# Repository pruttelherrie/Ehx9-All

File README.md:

## WARNING! 
Do not use the EEPROM store code from before 2021-10-01! It will eat up your flash writes like candy because of the braindead EEPROM.write lib in the stm32duino core. Fixed in callbacks.h and main.cpp, dd 2021-10-01

## Ehx9-All: combining and programming EHX '9' pedals

Electro Harmonix' 9 series of pedals is a range of polyphonic synthesis pedals for guitar. The
effects and sounds that can be obtained are superb, however they have a few shortcomings: 
first of all they are not programmable (i.e. there's only one setting, no way to store 
favourites and recall them quickly) and if you have more than one, they tend to take
up quite a lot of space on a pedalboard, especially if one uses them only sparingly
during a set.

The modifications documented in this repository try to eliminate these shortcomings.

## Programmability

To store and recall settings, the pots and switch are removed. GPIOs from the
microcontroller are connected to the main board to replace the functionality of
the pots and the switch. Since we use a PWM signal for the pots, it is low-pass
filtered by a simple first-order RC network.

Encoders take the place of the pots and the switch, a TFT is added for visual 
feedback of the settings.

## Space saving

All pedals of this serie share the same PCB. The difference is in the firmware of the
DSP. This firmware is stored in an EEPROM. By multiplexing multiple EEPROMS on one
board and resetting the DSP after switching the multiplexer, one can switch between
pedals of the series within one enclosure.

## Implementing the mods

Modding a pedal is not for the faint of heart. It is pretty easy to destroy the pedal
in the process. Also, a number of tools are needed:

* A way to program an Attiny2313. I use a Tuxgraphics AVR programmer, but there's a large number of other options.
* A way to program the STM32 blackpill. I use an ST-Link clone.
* There's SMD (de) soldering involved
* The enclosure is modified

## BOM

The BOMs for the PCBs can be found in their folders:
[controller](./controller-pcb/ibom.html)
[multiplexer](./multiplexer-pcb/ibom.html)

## Firmware

The multiplexer firmware was made with the Arduino IDE.

The controller firmware was made with VSCode + PlatformIO.

## Walkthrough of a mod

TBD: text and images.

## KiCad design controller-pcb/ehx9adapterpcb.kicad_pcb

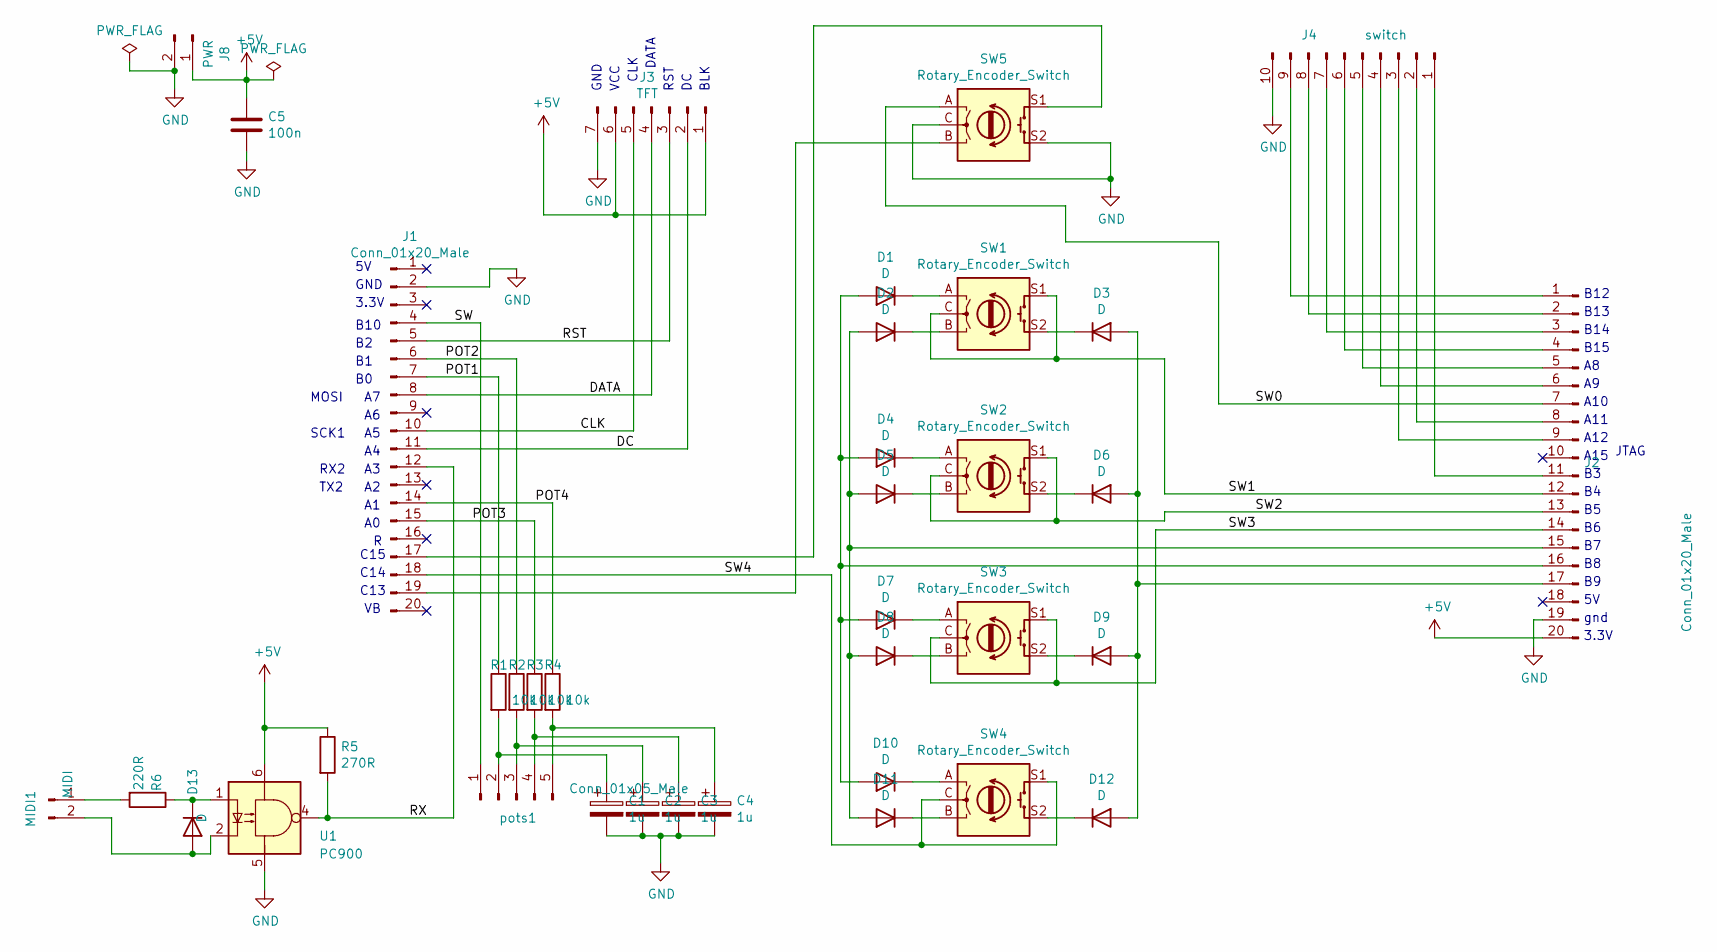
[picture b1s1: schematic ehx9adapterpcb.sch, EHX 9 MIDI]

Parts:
C1, C2, C3, C4: 1u; CP_Radial_D5.0mm_P2.50mm
C5: 100n; C_Rect_L7.0mm_W2.0mm_P5.00mm
D1, D2, D3, D4, D5, D6, D7, D8, D9, D10, D11, D12: D; D_DO-34_SOD68_P7.62mm_Horizontal
D13: D; D_DO-34_SOD68_P2.54mm_Vertical_KathodeUp
J1, J2: Conn_01x20_Male; PinHeader_1x20_P2.54mm_Vertical
J3: TFT; PinHeader_1x07_P2.54mm_Vertical
J4: switch; PinHeader_1x10_P2.54mm_Vertical
J8: PWR; PinHeader_1x02_P2.54mm_Vertical
MIDI1: MIDI; PinHeader_1x02_P2.54mm_Vertical
R1, R2, R3, R4: 10k; R_Axial_DIN0204_L3.6mm_D1.6mm_P2.54mm_Vertical
R5: 270R; R_Axial_DIN0204_L3.6mm_D1.6mm_P2.54mm_Vertical
R6: 220R; R_Axial_DIN0204_L3.6mm_D1.6mm_P2.54mm_Vertical
SW1, SW2, SW3, SW4, SW5: Rotary_Encoder_Switch; RotaryEncoder_Alps_EC11E-Switch_Vertical_H20mm
U1: PC900; DIP-6_W7.62mm_LongPads
pots1: Conn_01x05_Male; PinHeader_1x05_P2.54mm_Vertical

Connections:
+5V: C5.1, J2.20, J3.1, J3.6, J8.1, R5.1, U1.6
/CLK: J1.10, J3.5
/DATA: J1.8, J3.4
/DC: J1.11, J3.2
/POT1: J1.7, R1.1
/POT2: J1.6, R2.1
/POT3: J1.15, R3.1
/POT4: J1.14, R4.1
/RST: J1.5, J3.3
/RX: J1.12, R5.2, U1.4
/SW: J1.4, pots1.1
/SW0: J2.7, SW5.A
/SW1: J2.12, SW1.C, SW1.S1
/SW2: J2.13, SW2.C, SW2.S1
/SW3: J2.14, SW3.C, SW3.S1
/SW4: J1.18, SW4.C, SW4.S1
GND: C1.2, C2.2, C3.2, C4.2, C5.2, J1.2, J2.19, J3.7, J4.10, J8.2, SW5.C, SW5.S2, U1.5
unnamed: C1.1, R1.2, pots1.2
unnamed: C2.1, R2.2, pots1.3
unnamed: C3.1, R3.2, pots1.4
unnamed: C4.1, R4.2, pots1.5
unnamed: D1.1 (K), SW1.A
unnamed: D1.2 (A), D4.2 (A), D7.2 (A), D10.2 (A), J2.16
unnamed: D2.1 (K), SW1.B
unnamed: D3.1 (K), SW1.S2
unnamed: D4.1 (K), SW2.A
unnamed: D5.1 (K), SW2.B
unnamed: D6.1 (K), SW2.S2
unnamed: D7.1 (K), SW3.A
unnamed: D8.1 (K), SW3.B
unnamed: D9.1 (K), SW3.S2
unnamed: D10.1 (K), SW4.A
unnamed: D11.1 (K), SW4.B
unnamed: D2.2 (A), D5.2 (A), D8.2 (A), D11.2 (A), J2.15
unnamed: D12.1 (K), SW4.S2
unnamed: D3.2 (A), D6.2 (A), D9.2 (A), D12.2 (A), J2.17
unnamed: D13.1 (K), R6.1, U1.1
unnamed: D13.2 (A), MIDI1.2, U1.2
unnamed: J1.17, SW5.S1
unnamed: J1.19, SW5.B
unnamed: J2.1, J4.9
unnamed: J2.2, J4.8
unnamed: J2.3, J4.7
unnamed: J2.4, J4.6
unnamed: J2.5, J4.5
unnamed: J2.6, J4.4
unnamed: J2.8, J4.2
unnamed: J2.9, J4.3
unnamed: J2.11, J4.1
unnamed: MIDI1.1, R6.2

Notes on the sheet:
GND
3.3V
B10
C15
C14
C13
gnd
A15
A12
A11
A10
B15
B14
B13
B12
CLK
SCK1
BLK
RST
DATA
MOSI
VCC
TX2
RX2
JTAG

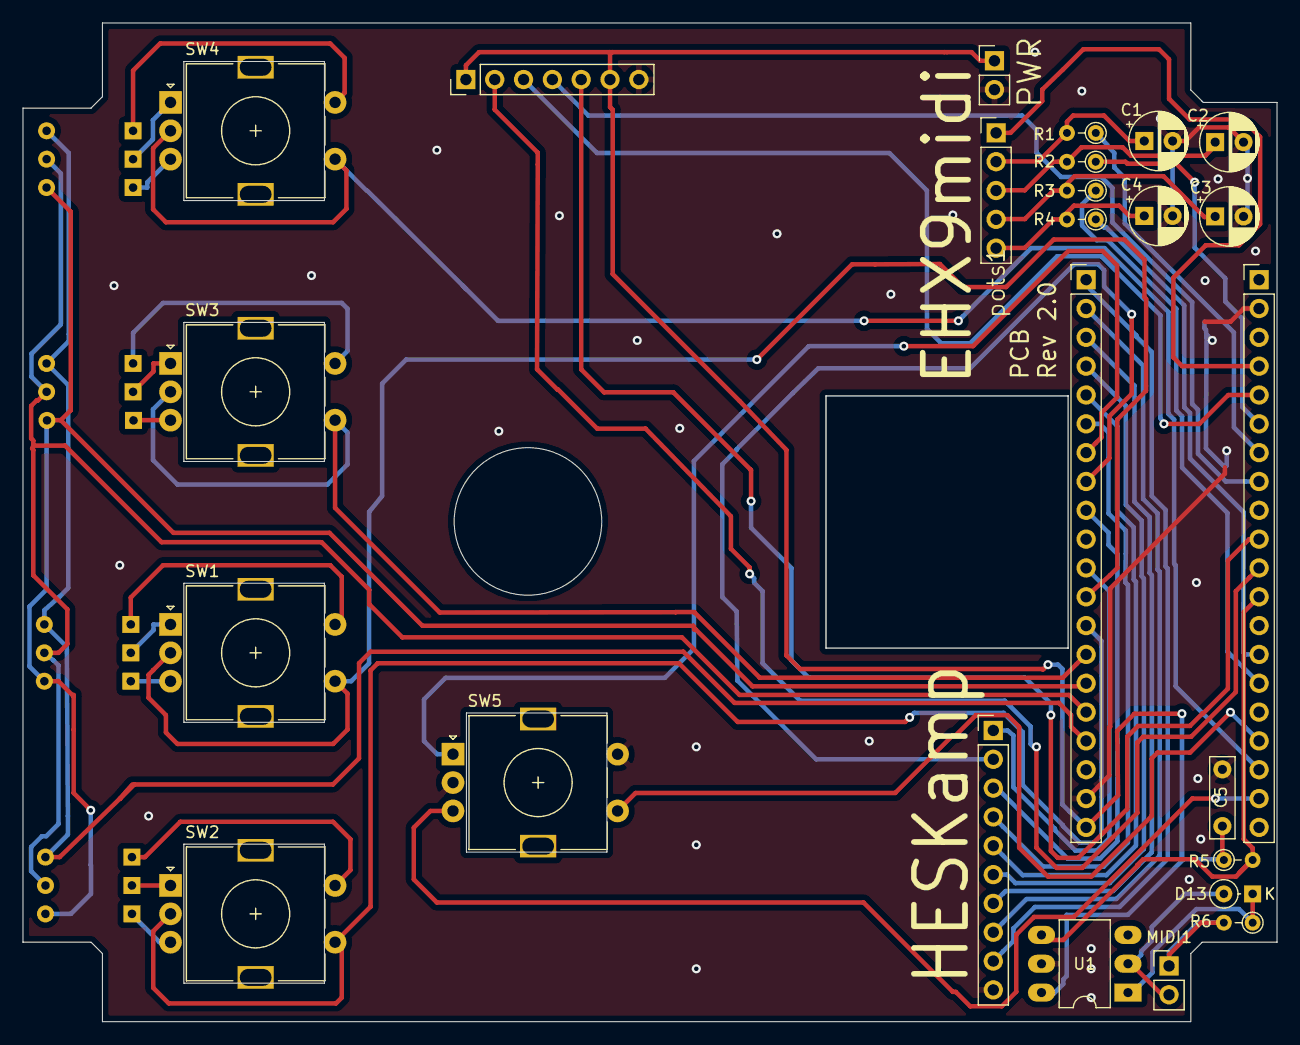
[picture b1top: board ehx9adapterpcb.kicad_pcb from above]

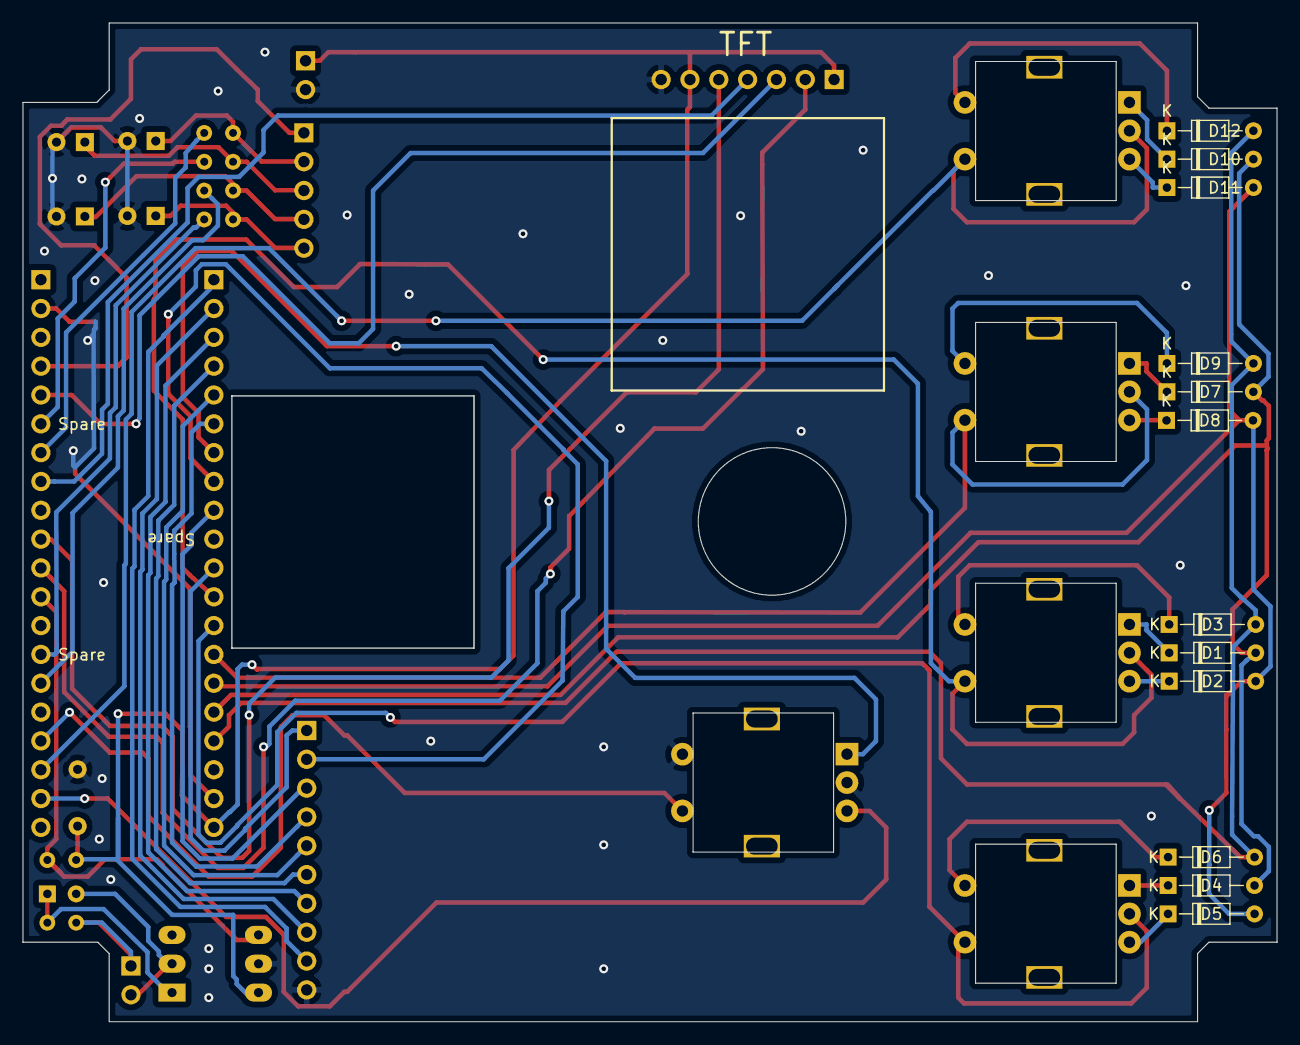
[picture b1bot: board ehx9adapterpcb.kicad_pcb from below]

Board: 2 copper layers, 110.5 x 88.0 mm, 37 parts (12 on the bottom side), 50 nets.

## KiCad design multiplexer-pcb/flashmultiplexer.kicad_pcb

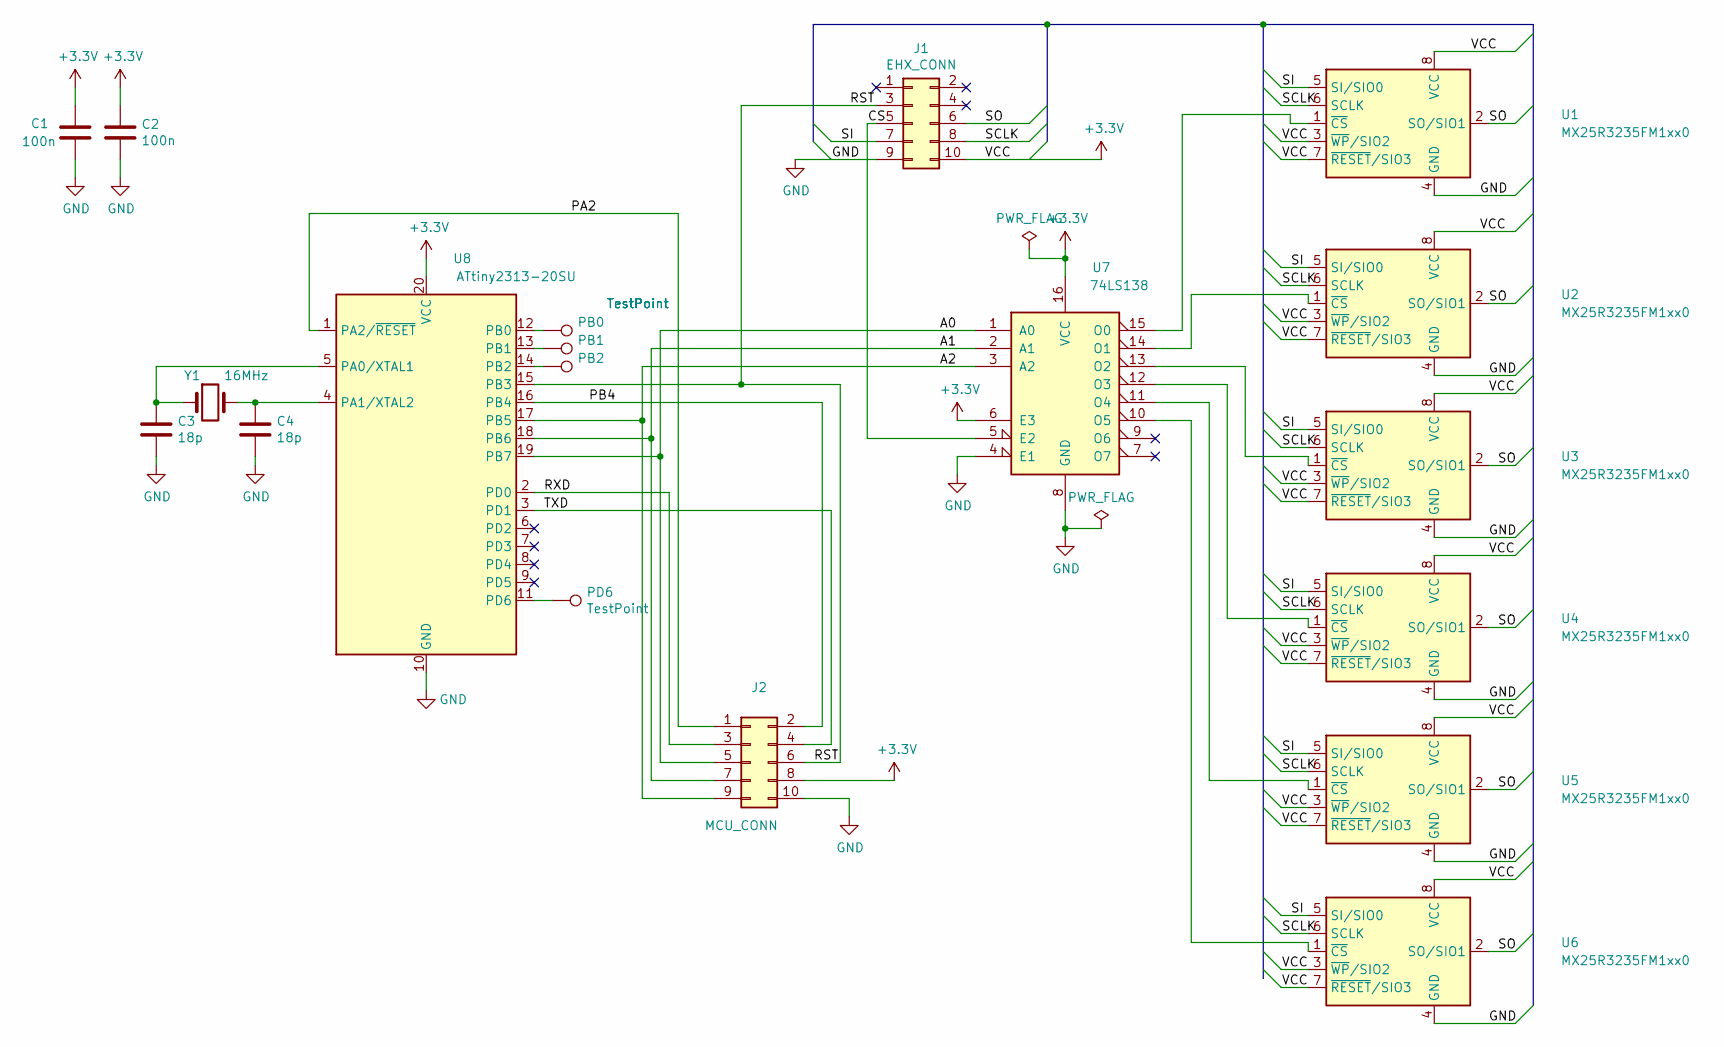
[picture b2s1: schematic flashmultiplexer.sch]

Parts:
C1, C2: 100n; C_1206_3216Metric
C3, C4: 18p; C_0805_2012Metric
J1: EHX_CONN; PinHeader_2x05_P2.54mm_Vertical
J2: MCU_CONN; PinHeader_2x05_P2.54mm_Horizontal
PB0, PB1, PB2: TestPoint; TestPoint_Pad_D1.5mm
PD6: TestPoint; TestPoint_Pad_D1.5mm
U1: MX25R3235FM1xx0; SOP-8_5.28x5.23mm_P1.27mm
U2, U3, U4, U5, U6: MX25R3235FM1xx0; SOP-8_3.9x4.9mm_P1.27mm
U7: 74LS138; SO-16_5.3x10.2mm_P1.27mm
U8: ATtiny2313-20SU; SOIC-20W_7.5x12.8mm_P1.27mm
Y1: 16MHz; Crystal_SMD_7050-2Pin_7.0x5.0mm_HandSoldering

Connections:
+3V3: C1.1, C2.1, J1.10, J2.8, U1.3 (~WP~/SIO2), U1.7 (~RESET~/SIO3), U1.8 (VCC), U2.3 (~WP~/SIO2), U2.7 (~RESET~/SIO3), U2.8 (VCC), U3.3 (~WP~/SIO2), U3.7 (~RESET~/SIO3), U3.8 (VCC), U4.3 (~WP~/SIO2), U4.7 (~RESET~/SIO3), U4.8 (VCC), U5.3 (~WP~/SIO2), U5.7 (~RESET~/SIO3), U5.8 (VCC), U6.3 (~WP~/SIO2), U6.7 (~RESET~/SIO3), U6.8 (VCC), U7.6 (E3), U7.16 (VCC), U8.20 (VCC)
/A0: J2.5, U7.1 (A0), U8.19 (PB7)
/A1: J2.7, U7.2 (A1), U8.18 (PB6)
/A2: J2.9, U7.3 (A2), U8.17 (PB5)
/CS: J1.5, U7.5 (E2)
/PA2: J2.1, U8.1 (PA2/~RESET)
/PB4: J2.2, U8.16 (PB4)
/RST: J1.3, J2.6, U8.15 (PB3)
/RXD: J2.3, U8.2 (PD0)
/SCLK: J1.8, U1.6 (SCLK), U2.6 (SCLK), U3.6 (SCLK), U4.6 (SCLK), U5.6 (SCLK), U6.6 (SCLK)
/SI: J1.7, U1.5 (SI/SIO0), U2.5 (SI/SIO0), U3.5 (SI/SIO0), U4.5 (SI/SIO0), U5.5 (SI/SIO0), U6.5 (SI/SIO0)
/SO: J1.6, U1.2 (SO/SIO1), U2.2 (SO/SIO1), U3.2 (SO/SIO1), U4.2 (SO/SIO1), U5.2 (SO/SIO1), U6.2 (SO/SIO1)
/TXD: J2.4, U8.3 (PD1)
GND: C1.2, C2.2, C3.2, C4.2, J1.9, J2.10, U1.4 (GND), U2.4 (GND), U3.4 (GND), U4.4 (GND), U5.4 (GND), U6.4 (GND), U7.4 (E1), U7.8 (GND), U8.10 (GND)
unnamed: C3.1, U8.5 (PA0/XTAL1), Y1.1
unnamed: C4.1, U8.4 (PA1/XTAL2), Y1.2
unnamed: PB0.1, U8.12 (PB0)
unnamed: PB1.1, U8.13 (PB1)
unnamed: PB2.1, U8.14 (PB2)
unnamed: PD6.1, U8.11 (PD6)
unnamed: U1.1 (~CS), U7.15 (O0)
unnamed: U2.1 (~CS), U7.14 (O1)
unnamed: U3.1 (~CS), U7.13 (O2)
unnamed: U4.1 (~CS), U7.12 (O3)
unnamed: U5.1 (~CS), U7.11 (O4)
unnamed: U6.1 (~CS), U7.10 (O5)

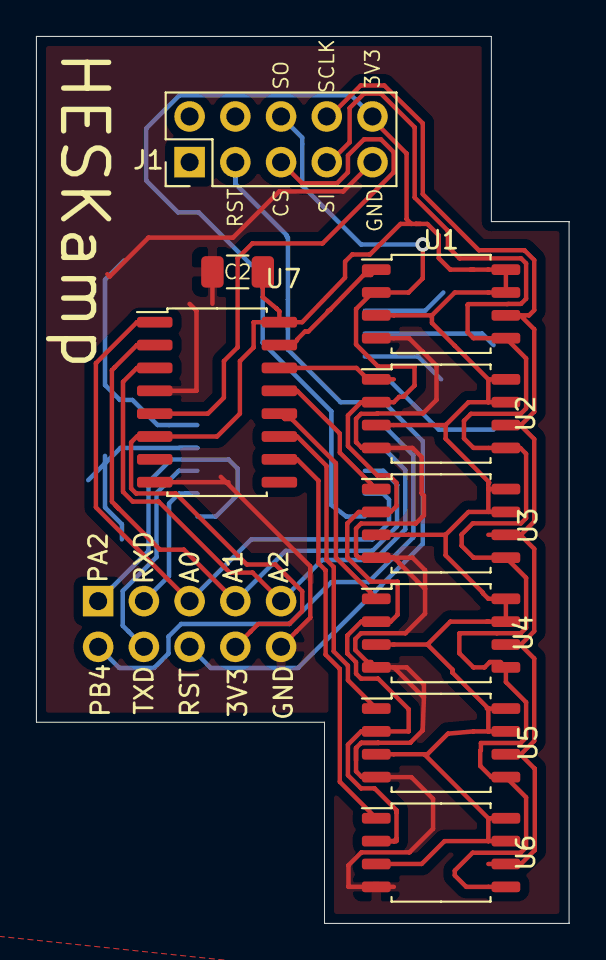
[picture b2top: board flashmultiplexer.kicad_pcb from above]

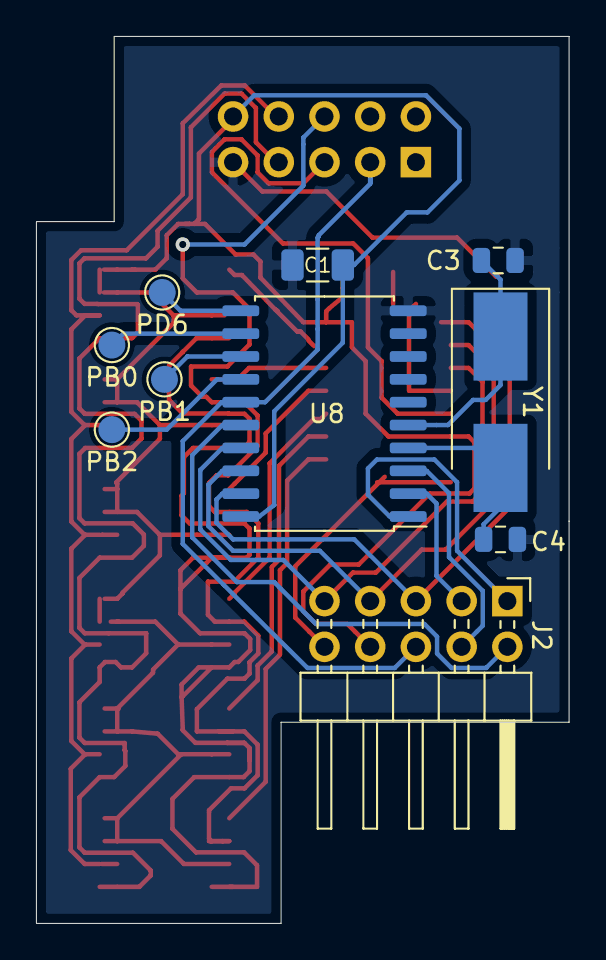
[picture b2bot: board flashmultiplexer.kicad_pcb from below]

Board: 2 copper layers, 29.6 x 49.3 mm, 19 parts (10 on the bottom side), 26 nets.

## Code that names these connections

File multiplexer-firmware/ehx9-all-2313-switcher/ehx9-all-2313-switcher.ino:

/*
 * https://forum.arduino.cc/t/attiny-25-45-85-2313-pin-numbers/81499/4
 * 
 * #define PIN_D0  ( 0)
 * #define PIN_D1  ( 1)
 * #define PIN_A1  ( 2)
 * #define PIN_A0  ( 3)
 * #define PIN_D2  ( 4)
 * #define PIN_D3  ( 5)
 * #define PIN_D4  ( 6)
 * #define PIN_D5  ( 7)
 * #define PIN_D6  ( 8)
 * #define PIN_B0  ( 9)
 * #define PIN_B1  (10)
 * #define PIN_B2  (11)
 * #define PIN_B3  (12)
 * #define PIN_B4  (13)
 * #define PIN_B5  (14)
 * #define PIN_B6  (15)
 * #define PIN_B7  (16)
 * #define PIN_A2  (17) 
 */

#define Addr0       16 // PB7
#define Addr1       15 // PB6
#define Addr2       14 // PB5

#define LED1         9 // PB0
#define LED2        10 // PB1
#define LED3        11 // PB2

#define RST_DSP     12 // PB3
#define SWITCH      13 // PB4

#define NUM_FLASH 4

uint8_t address = 0;

void setPedal(uint8_t address) {
    digitalWrite(Addr0, (address & 1) == 1);
    digitalWrite(Addr1, (address & 2) == 2);
    digitalWrite(Addr2, (address & 4) == 4);

    switch(address) {
        default:
        case 0:
            digitalWrite(LED1, LOW);
            digitalWrite(LED2, HIGH);
            digitalWrite(LED3, HIGH);
            break;
        case 1:
            digitalWrite(LED1, HIGH);
            digitalWrite(LED2, LOW);
            digitalWrite(LED3, HIGH);
            break;
        case 2:
            digitalWrite(LED1, HIGH);
            digitalWrite(LED2, HIGH);
            digitalWrite(LED3, LOW);
            break;
        case 3:
            digitalWrite(LED1, LOW);
            digitalWrite(LED2, HIGH);
            analogWrite(LED3, 5);
            break;
    }
    
    digitalWrite(RST_DSP, LOW);
    pinMode(RST_DSP, OUTPUT); // Pull low
    delay(10);
    pinMode(RST_DSP, INPUT);
    delay(250);
}

void setup() {
    pinMode(Addr0, OUTPUT);
    pinMode(Addr1, OUTPUT);
    pinMode(Addr2, OUTPUT);

    pinMode(LED1, OUTPUT);
    pinMode(LED2, OUTPUT);
    pinMode(LED3, OUTPUT);
    
    pinMode(RST_DSP, INPUT); // Hi-Z
    pinMode(SWITCH, INPUT_PULLUP);

    setPedal(address);
}



void loop() {
    if(digitalRead(SWITCH) == LOW) {
         if(++address >= NUM_FLASH) { 
             address = 0;
         }
         setPedal(address);
    }
}

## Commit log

2021-10-01 Add warning
2021-10-01 fixed thrashing of flash with EEPROM.write in stm32duino
2021-10-01 add eeprom thrashing warning
2021-10-01 fixed typo
